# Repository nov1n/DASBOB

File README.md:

# DASBOB

This is a modification of the DASBOB keyboard. I adapted the routing to work with nice!nanos and ZMK, and routed the outer terminals of the TRRS connector to the RAW and GND pins. This way you can use a stripped TRRS cable to connect the boards to the batteries.

## Firmware
The routing matches that of the rae-dux keyboard. To configure this in ZMK please use this shield: https://github.com/andrewjrae/zmk-config/tree/development/config.

## Batteries and case
To find the wires of the stripped TRRS cable that connect to the RAW and GND pins it's easiest to use a multimeter in continuity mode. Hold one probe on the RAW pin, and the other on each of the wires in turn, until you hear a beep. Repeat for the GND pin. Then connect these wires to the positive and the negative terminals of your battery respectively.

An optional Magic Trackpad accommodates two 90x60x3mm 3000mAh lipo batteries. You can find the design here: (link: https://www.printables.com/model/460594-magic-trackpad-battery-case).

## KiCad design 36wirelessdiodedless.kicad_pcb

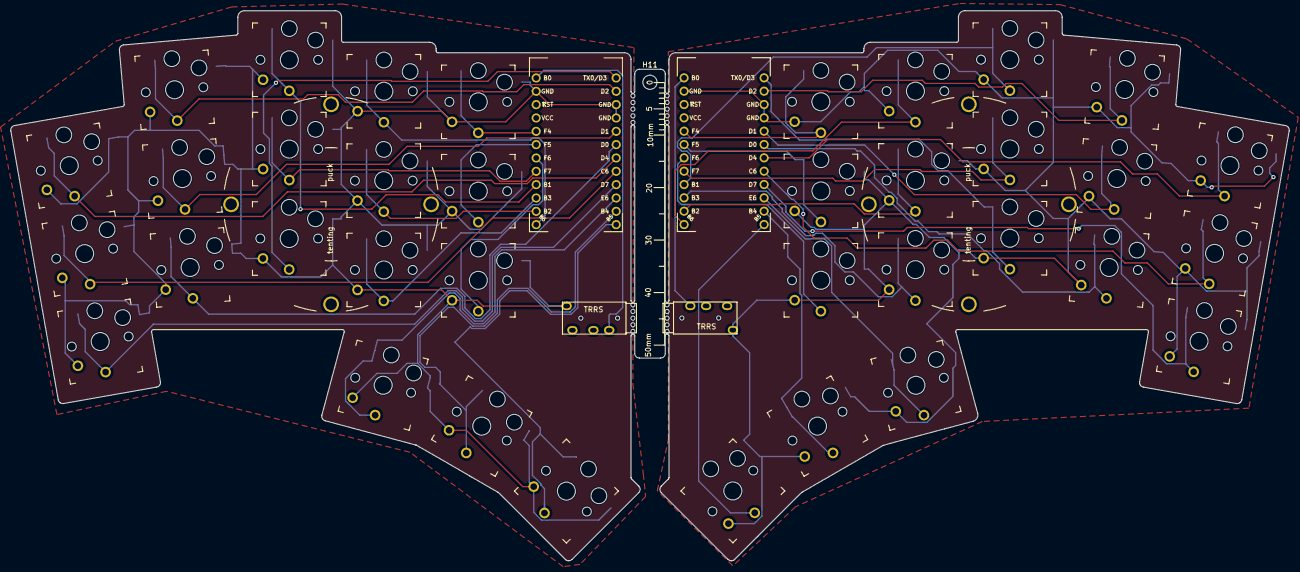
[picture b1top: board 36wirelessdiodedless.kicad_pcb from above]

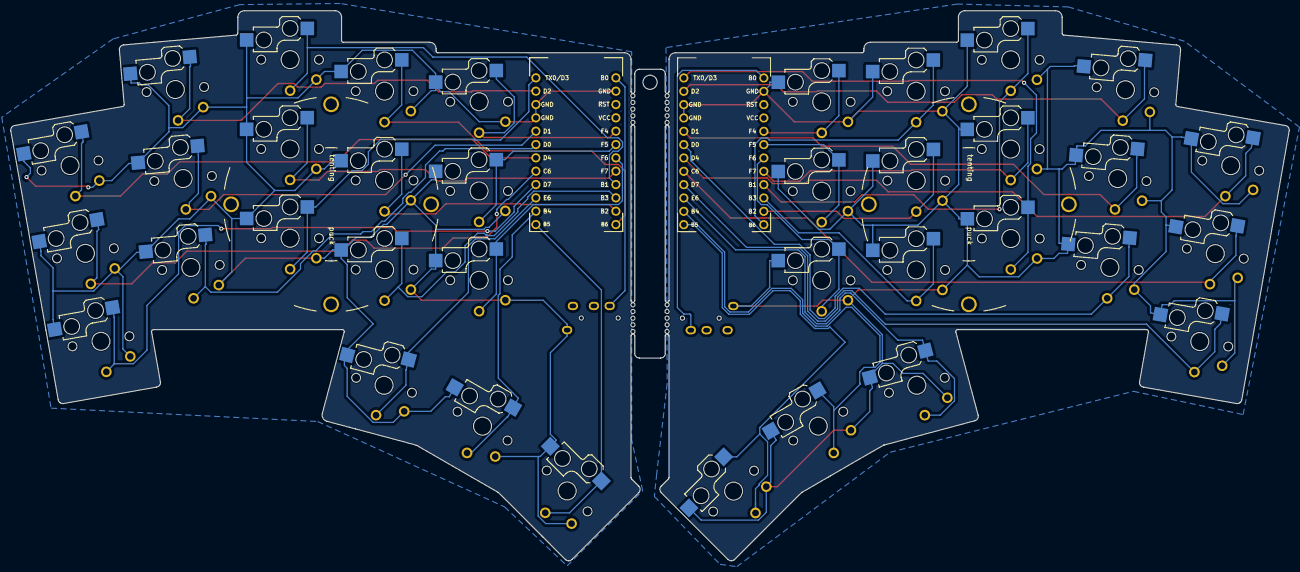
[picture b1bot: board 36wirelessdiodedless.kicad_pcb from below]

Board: 2 copper layers, 243.5 x 104.8 mm, 48 parts (2 on the bottom side), 40 nets.

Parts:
H1, H2, H9, H10: Mousebites; breakaway-mousebites
H11: M3 MountingHole; MountingHole_2.7mm_M2.5_DIN965
H12: Ruler; Gauge_50mm_Type1_SilkScreenTop
J1, J2: TRRS LEFT; TRRS-PJ-320A
SW1, SW2, SW3, SW4, SW5, SW6, SW7, SW8, SW9, SW10, SW11, SW12, SW13, SW14, SW15, SW16, SW17, SW18, SW19, SW20, SW21, SW22, SW23, SW24, SW25, SW26, SW27, SW28, SW29, SW30, SW31, SW32, SW33, SW34, SW35, SW36: SW_Push; Kailh_socket_PG1350_optional
U1: Elite-C RIGHT; Elite-C
U2: Elite-C LEFT; Elite-C
puck1, puck2: Hole; Tenting_Pucksmol

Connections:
GND: J1.1 (S), SW1.2, SW2.2, SW3.2, SW4.2, SW5.2, SW6.2, SW7.2, SW8.2, SW9.2, SW10.2, SW11.2, SW12.2, SW13.2, SW14.2, SW15.2, SW16.2, SW17.2, SW18.2, U1.2 (GND), U1.15 (GND), U1.16 (GND)
GNDR: J2.1 (S), SW19.2, SW20.2, SW21.2, SW22.2, SW23.2, SW24.2, SW25.2, SW26.2, SW27.2, SW28.2, SW29.2, SW30.2, SW31.2, SW32.2, SW33.2, SW34.2, SW35.2, SW36.2, U2.2 (GND), U2.15 (GND), U2.16 (GND)
P0: SW2.1, U1.14 (RX1/PD2)
P0R: SW22.1, U2.14 (RX1/PD2)
P1: SW13.1, U1.13 (TX0/PD3)
P1R: SW31.1, U2.13 (TX0/PD3)
P2: SW7.1, U1.17 (2/PD1)
P2R: SW27.1, U2.17 (2/PD1)
P3: SW12.1, U1.18 (3/PD0)
P3R: SW32.1, U2.18 (3/PD0)
P4: SW1.1, U1.19 (4/PD4)
P4R: SW23.1, U2.19 (4/PD4)
P5: SW6.1, U1.20 (5/PC6)
P5R: SW28.1, U2.20 (5/PC6)
P6: SW11.1, U1.21 (6/PD7)
P6R: SW33.1, U2.21 (6/PD7)
P7: SW16.1, U1.22 (7/PE6)
P7R: SW36.1, U2.22 (7/PE6)
P8: SW17.1, U1.23 (8/PB4)
P8R: SW35.1, U2.23 (8/PB4)
P9: SW18.1, U1.24 (9/PB5)
P9R: SW34.1, U2.24 (9/PB5)
P10: SW4.1, U1.12 (10/PB6)
P10R: SW20.1, U2.12 (10/PB6)
P14: SW14.1, U1.10 (14/PB3)
P14R: SW30.1, U2.10 (14/PB3)
P15: SW3.1, U1.9 (15/PB1)
P15R: SW21.1, U2.9 (15/PB1)
P16: SW9.1, U1.11 (16/PB2)
P16R: SW25.1, U2.11 (16/PB2)
P18: SW8.1, U1.8 (A0/PF7)
P18R: SW26.1, U2.8 (A0/PF7)
P19: SW15.1, U1.7 (A1/PF6)
P19R: SW29.1, U2.7 (A1/PF6)
P20: SW10.1, U1.6 (A2/PF5)
P20R: SW24.1, U2.6 (A2/PF5)
P21: SW5.1, U1.5 (A3/PF4)
P21R: SW19.1, U2.5 (A3/PF4)
RAW: J1.4 (R2), U1.1 (B0)
RAWR: J2.4 (R2), U2.1 (B0)

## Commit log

2023-05-14 Add modified version
2023-05-15 Add gerbers
2023-05-15 Refill zones
